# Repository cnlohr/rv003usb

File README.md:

# Using USB on the CH32V003

Ever wanted a 10 cent USB low-speed capable processor? Well, look no further. RV003USB allows you to, in firmware, connect a 10 cent RISC-V to a computer with USB. It is fundamentally just a pin-change interrupt routine that runs in assembly, and some C code to handle higher level functionality.

### It's small!

The bootloader version of the tool can create a HID device, enumerate and allow execution of code on-device in 1,920 bytes of code. Basic HID setups are approximately 2kB, like the Joystick demo.

### It's simple!

The core assembly code is very basic, having both an [interrupt](https://github.com/cnlohr/rv003usb/blob/master/rv003usb/rv003usb.S#L43) and [code to send](https://github.com/cnlohr/rv003usb/blob/master/rv003usb/rv003usb.S#L547). Additionally only around [250 lines of C](https://github.com/cnlohr/rv003usb/blob/master/rv003usb/rv003usb.c) code to facilitate the rest of the USB protocol.

### It's adaptable!

The [core assembly](https://github.com/cnlohr/rv003usb/blob/master/rv003usb/rv003usb.S) code is standardized, and there is also [a c file](https://github.com/cnlohr/rv003usb/blob/master/rv003usb/rv003usb.c) code, to handle different functionality with hid feature requests, control setup events, interrupt endpoints (send and receive) are all done in.

It shows both how to be a normal USB device, as well as how to write programs to run on your PC that can talk to your USB device.

### It requires very little hardware!

 * `U1` is a CH32V003
 * `J1` is a USB type C connector.
 * `R1` 1.5k 5% is required under all configurations, though it may connect D- to DPU or VCC if the intent is for the part to always be on-bus.
 * `U2`, `C1`, `C2` are used to run the CH32V003 at 3.3V.  For USB it should not be run beyond 3.6V.
 * `R2`, `R3` 5.1k resistors are only needed if using a type C connector and you want the host to provide 5V power.

It even supports the SOIC-8 - see this thread: https://github.com/cnlohr/rv003usb/issues/25#issuecomment-1779130408

Optionally 33 or 47 ohm resistors may be placed in-series with D+ and D- to the port to reduce noise and help protect the chip.

### It's configurable

The Pins (Port and GPIO number) used for USB are configured in `usb_config.h`.

~~~C
#define USB_PORT D     // [A,C,D] GPIO Port to use with D+, D- and DPU
#define USB_PIN_DP 3   // [0-4] GPIO Number for USB D+ Pin
#define USB_PIN_DM 4   // [0-4] GPIO Number for USB D- Pin
#define USB_PIN_DPU 5  // [0-7] GPIO for feeding the 1.5k Pull-Up on USB D- Pin; Comment out if not used / tied to 3V3!
~~~

All configured pins need to be on the same GPIO port.

> [!CAUTION]
> Only GPIOs 0-4 can be used for USB D+/D- due to limits of the [c.andi](https://msyksphinz-self.github.io/riscv-isadoc/html/rvc.html#c-andi) instruction which can only hold a 5 bit value. 
> You **cannot use** PC5-PC7 and PD5-PD7 for D+/D-!

A 1,5k pull-up on D- is used to signal the presence of a USB low-speed device on the bus. `USB_PIN_DPU` is designed to control this pull-up, but this is optional. You have three options here:

1. Use `USB_PIN_DPU` to let RV003USB controll the GPIO. You're limited to using the same port as for D+/D-.
2. Comment out `USB_PIN_DPU` and tie the pull-up to 3V3. This frees a GPIO completely and signals device presence constantly. 
3. Comment out `USB_PIN_DPU` and tie it to a GPIO of your choice - even on a different port. You have to signal device presence in your own user-code though.

Even with the pull-up tied to 3V3 you can trigger a USB re-enumeration by pulsing D- low in user-code. Add the otherwise optional 33/47 ohm inline resistors on D+/D- if you plan on doing this!

See [bootloader](bootloader) for additional considerations on the pin configuration if you plan to use the USB bootloader!

> [!NOTE]
> Use `make clean` before `make` whenever you change the configuration in `usb_config.h`

### It's got demos!

Here are the following demos and their statuses...

| Example      | Description | ❖ | 🐧 |
| ------------ | ----------- | --------------- | ------------- |
| [demo_gamepad](https://github.com/cnlohr/rv003usb/tree/master/demo_gamepad) | Extremely simple example, 2-axis gamepad + 8 buttons | `✅` | `✅` |
| [demo_composite_hid](https://github.com/cnlohr/rv003usb/tree/master/demo_composite_hid) | Mouse and Keyboard in one device | `✅` | `✅` |
| [demo_hidapi](https://github.com/cnlohr/rv003usb/tree/master/demo_hidapi) | Write code to directly talk to your project with fully-formed messages. (Works on [Android](https://github.com/cnlohr/androidusbtest)) (Includes WebUSB Demo) | `✅` | `✅` |
| [bootloader](https://github.com/cnlohr/rv003usb/tree/master/bootloader) | CH32V003 Self-bootloader, able to flash itself with minichlink | `✅` | `✅` |

And the following largely incomplete, but proof-of-concept projects:

| Example      | Description | ❖ | 🐧 |
| ------------ | ----------- | --------------- | ------------- |
| [cdc_exp](https://github.com/cnlohr/rv003usb/tree/master/testing/cdc_exp) | Enumerate as a USB Serial port and send and receive Data (incomplete, very simple) | `⚠️` | `✅` | :question: |
| [usb_cdc_uart](https://github.com/cnlohr/rv003usb/tree/master/testing/usb_cdc_uart) | Enumerate as a USB to UART bridge (115200 baud) (very similar issues to cdc_exp, only slightly more complete, tested on linux) | `⚠️` | `✅` | :question: |
| [demo_midi](https://github.com/cnlohr/rv003usb/tree/master/testing/demo_midi) | MIDI-IN and MIDI-OUT | `✅` | `✅` |
| [test_ethernet](https://github.com/cnlohr/rv003usb/tree/master/testing/test_ethernet) | RNDIS Device (note: VERY SLOW) | `⚠️` | `✅` |

Note: CDC In windows likely CAN work, but I can't figure out how to do it.  Linux explicitly blacklists all low-speed USB Ethernet that I could find.  The MIDI example only demonstrates MIDI-OUT.

### It's built on ch32v003fun

[ch32v003fun](https://github.com/cnlohr/ch32v003fun) is a minimal development SDK of sorts for the CH32V003, allowing for maximum flexability without needing lots of code surrounding a HAL.

## General developer notes

### Care surrounding interrupts and critical sections.

You are allowed to use interrupts and have critical sections, however, you should keep critical sections to approximately 40 or fewer cycles if possible.  Additionally if you are going to be using interrupts that will take longer than about 40 cycles to execute, you must enable preemption on that interrup.  For an example of how that works you can check the ws2812b SPI DMA driver in ch32v003fun.  The external pin-chane-interrupt **must** be the highest priority. And it **must never** be preempted.  While it's OK to have a short delay before it is fired, interrupting the USB reception code mid-transfer is prohibited.

### Modifying headers / `usb_config.h`

Note that if you change the pin assignments for your custom hardware in `usb_config.h`, you will need to run `make clean` afterwards (and then run `make`).

## It's still in beta.

This project is not ready for prime time, though it is sort of in a beta phase.  Proof of concept works, lots of demos work.  Maybe you can help out!

`✅` Able to go on-bus and receive USB frames  
`✅` Compute CRC in-line while receiving data  
`✅` Bit Stuffing (Works, tested)  
`✅` Sending USB Frames  
`✅` High Level USB Stack in C  
`✅` Make USB timing more precise.  
`✅` Use SE0 1ms ticks to tune HSItrim  
`✅` Rework sending code to send tokens/data separately.  
`✅` Fix CRC Code  
`✅` Make minichlink able to use bootloader.  
`✅` Optimize high-level stack.  
`✅` Fit in bootloader (NOTE: Need to tighten more)  
`✅` Do basic retiming, at least in preamble to improve timing.  
`✅` Use HID custom messages.  
`✅` Improve sync sled.  I.e. coarse and fine sledding.  
`✅` Abort on non-8-bit-aligned-frames.  
`✅` Make more demos  
`✅` API For self-flashing + `🔳` printf from bootloader  
`🔳` Improve timing on send, for CRC bits.  Currently we are off by about 6 cycles total.  
`❕` Further optimize Send/Receive PHY code. (Please help) 
`❕` Consider a timer-only approach (may never happen)
`⚠️` Enable improved retiming (Requires a few more cycles) (Please help!)  
`⚠️`  Arduino support (someone else will have to take this on)

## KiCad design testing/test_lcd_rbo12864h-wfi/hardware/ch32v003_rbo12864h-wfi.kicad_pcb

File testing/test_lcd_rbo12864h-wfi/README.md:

# rbo12864h-wfi video driver for Linux

You can flash this firmware on a ch32v003 and hook it up to an RBO12864H-WFI.

The display is available from https://www.ronboe.com/ they are very inexpensive but you have to ask for them.

1. Optionally you can flash the bootloader so you can continue to work on this program later.
2. Flash this code to the ch32v003.
3. cd host
4. sudo ./host

The controls allow you to change the contrast, resistor ratio, backlight brightness and cutoff for black/white.

Schematics are located in the hardware/ folder.

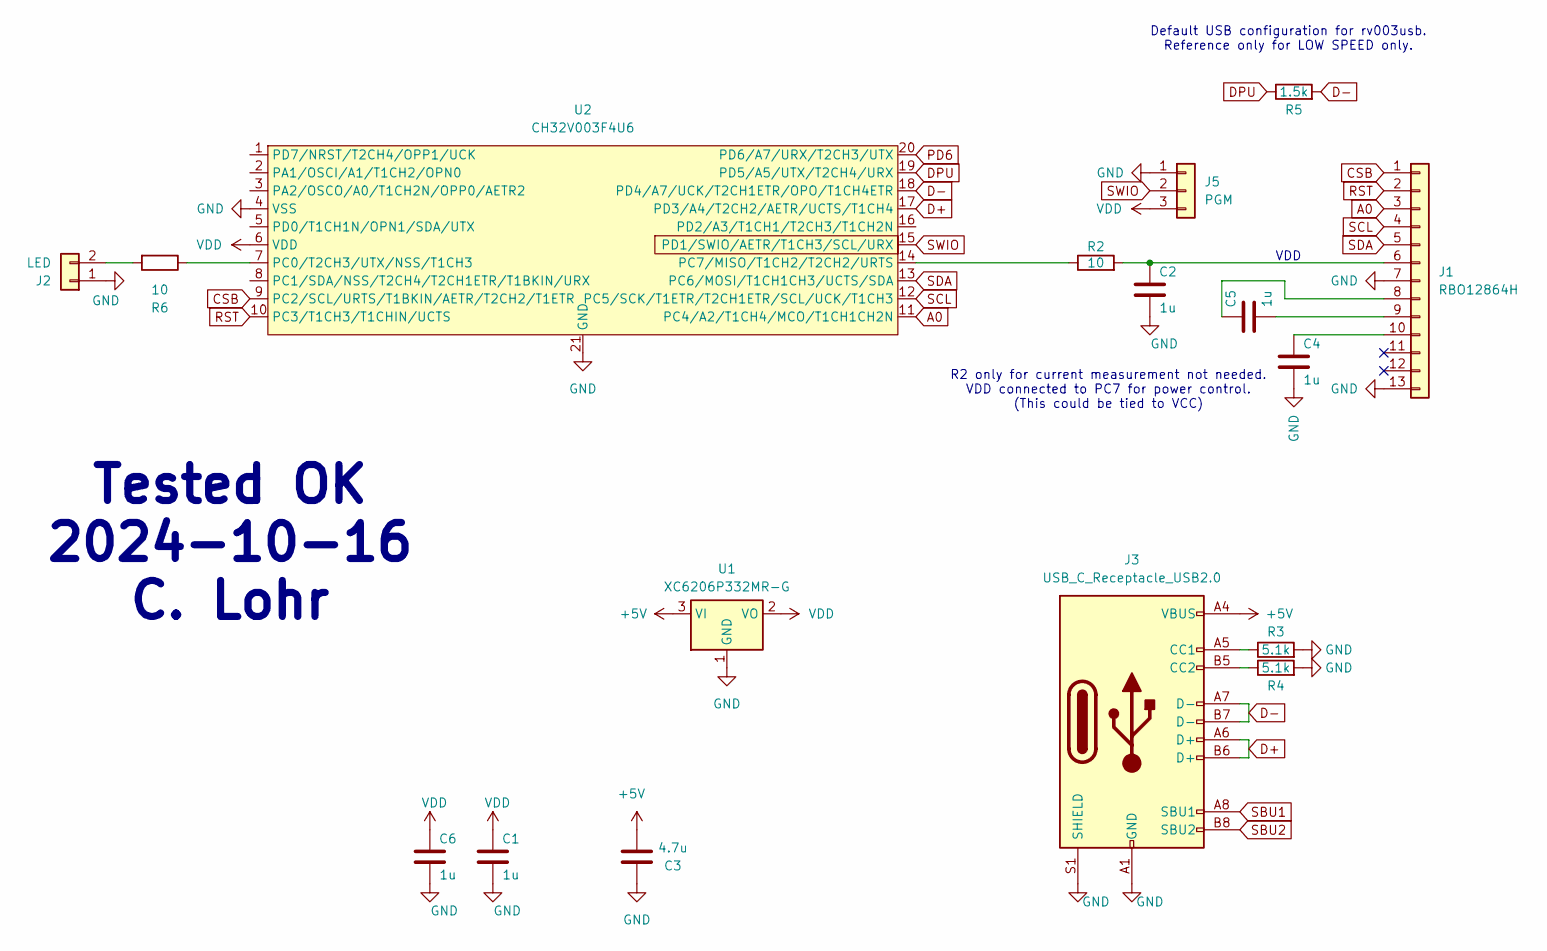
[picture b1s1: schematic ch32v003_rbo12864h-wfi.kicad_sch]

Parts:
C1, C2, C4, C5, C6: 1u; R_0402_1005Metric; LCSC C52923
C3: 4.7u; R_0402_1005Metric; LCSC C23733
J1: RBO12864H; RBO12864H-WFI
J2: LED; PinHeader_1x02_P2.00mm_Vertical
J3: USB_C_Receptacle_USB2.0; USB_C_Receptacle_HRO_TYPE-C-31-M-12; LCSC C2765186
J5: PGM; PinHeader_1x03_P2.54mm_Vertical
R2, R6: 10; R_0402_1005Metric; LCSC C25077
R3, R4: 5.1k; R_0402_1005Metric; LCSC C25905
R5: 1.5k; R_0402_1005Metric; LCSC C25867
U1: XC6206P332MR-G; SOT-23; LCSC C5446
U2: CH32V003F4U6; QFN-20-1EP_3x3mm_P0.4mm_EP1.65x1.65mm; LCSC C5299908

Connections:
+5V: C3.2, J3.A4 (VBUS), J3.A9 (VBUS), J3.B4 (VBUS), J3.B9 (VBUS), U1.3 (VI)
A0: J1.3, U2.11 (PC4/A2/T1CH4/MCO/T1CH1CH2N)
CSB: J1.1, U2.9 (PC2/SCL/URTS/T1BKIN/AETR/T2CH2/T1ETR)
D+: J3.A6 (D+), J3.B6 (D+), U2.17 (PD3/A4/T2CH2/AETR/UCTS/T1CH4)
D-: J3.A7 (D-), J3.B7 (D-), R5.2, U2.18 (PD4/A7/UCK/T2CH1ETR/OPO/T1CH4ETR)
DPU: R5.1, U2.19 (PD5/A5/UTX/T2CH4/URX)
GND: C1.1, C2.1, C3.1, C4.1, C6.1, J1.7, J1.13, J2.1, J3.A1 (GND), J3.A12 (GND), J3.B1 (GND), J3.B12 (GND), J3.S1 (SHIELD), J5.1, R3.2, R4.2, U1.1 (GND), U2.4 (VSS), U2.21 (GND)
unnamed: C2.2, J1.6, R2.2
unnamed: C5.2, J1.8
unnamed: C5.1, J1.9
unnamed: C4.2, J1.10
unnamed: J2.2, R6.2
unnamed: J3.A5 (CC1), R3.1
unnamed: J3.B5 (CC2), R4.1
unnamed: R6.1, U2.7 (PC0/T2CH3/UTX/NSS/T1CH3)
unnamed: R2.1, U2.14 (PC7/MISO/T1CH2/T2CH2/URTS)
PD6: U2.20 (PD6/A7/URX/T2CH3/UTX)
RST: J1.2, U2.10 (PC3/T1CH3/T1CHIN/UCTS)
SBU1: J3.A8 (SBU1)
SBU2: J3.B8 (SBU2)
SCL: J1.4, U2.12 (PC5/SCK/T1ETR/T2CH1ETR/SCL/UCK/T1CH3)
SDA: J1.5, U2.13 (PC6/MOSI/T1CH1CH3/UCTS/SDA)
SWIO: J5.2, U2.15 (PD1/SWIO/AETR/T1CH3/SCL/URX)
VDD: C1.2, C6.2, J5.3, U1.2 (VO), U2.6 (VDD)

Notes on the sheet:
Tested OK 2024-10-16 C. Lohr
Default USB configuration for rv003usb. Reference only for LOW SPEED only.
VDD
R2 only for current measurement not needed. VDD connected to PC7 for power control. (This could be tied to VCC)

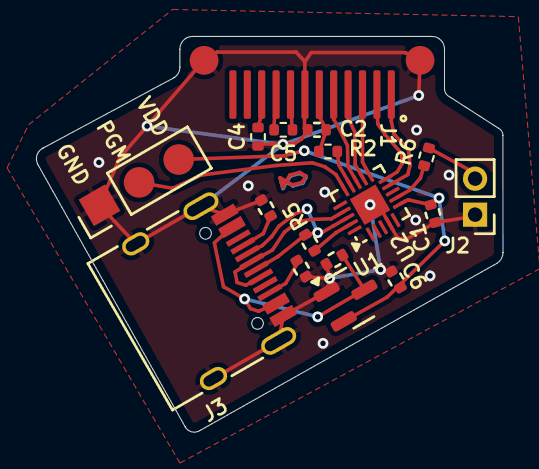
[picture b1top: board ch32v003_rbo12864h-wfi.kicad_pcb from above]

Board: 2 copper layers, 25.9 x 22.0 mm, 17 parts (0 on the bottom side), 21 nets.

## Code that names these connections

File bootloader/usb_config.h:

#ifndef _USB_CONFIG_H
#define _USB_CONFIG_H

//Defines the number of endpoints for this device. (Always add one for EP0). For two EPs, this should be 3.  For one, 2.
#define ENDPOINTS 2

/*	
	CH32V003FUN DevBoard:
	PD3 D+
	PD4 D-
	PD5 D-_PU

	CH32V003J4M6:
	PC1 D+
	PC2 D-
	PC4 D-_PU
*/

#define USB_PORT D     // [A,C,D] GPIO Port to use with D+, D- and DPU
#define USB_PIN_DP 3   // [0-4] GPIO Number for USB D+ Pin
#define USB_PIN_DM 4   // [0-4] GPIO Number for USB D- Pin
//#define USB_PORT_DPU A  // [A,C,D] Override GPIO Port for DPU
#define USB_PIN_DPU 5  // [0-7] GPIO for feeding the 1.5k Pull-Up on USB D- Pin; Comment out if not used / tied to 3V3!

#define RV003USB_OPTIMIZE_FLASH 1

#ifndef __ASSEMBLER__

#include <tinyusb_hid.h>

#ifdef INSTANCE_DESCRIPTORS
//Taken from http://www.usbmadesimple.co.uk/ums_ms_desc_dev.htm
static const uint8_t device_descriptor[] = {
	18, //Length
	1,  //Type (Device)
	0x00, 0x02, //Spec (bcdUSB)
	0x0, //Device Class
	0x0, //Device Subclass
	0x0, //Device Protocol  (000 = use config descriptor)
	0x08, //Max packet size for EP0 (This has to be 8 because of the USB Low-Speed Standard)
	0x09, 0x12, //ID Vendor   //TODO: register this in http://pid.codes/howto/ or somewhere.
	0x03, 0xb0, //ID Product
	0x00, 0x00, //ID Rev (bcdDevice)
	1, //Manufacturer string
	2, //Product string
	3, //Serial string
	1, //Max number of configurations
};


static const uint8_t special_hid_desc[] = { 
  HID_USAGE_PAGE ( HID_USAGE_PAGE_DESKTOP      )                 ,
  HID_USAGE      ( 0xff  )                 , // Needed?
  HID_COLLECTION ( HID_COLLECTION_APPLICATION )                 ,
    HID_REPORT_SIZE ( 8 ),
    HID_REPORT_COUNT ( 127 ) ,
    HID_REPORT_ID    ( 0xaa                                   )
    HID_USAGE        ( 0xff              ) ,
    HID_FEATURE      ( HID_DATA | HID_ARRAY | HID_ABSOLUTE    ) ,
  HID_COLLECTION_END
};


static const uint8_t config_descriptor[] = {  //Mostly stolen from a USB mouse I found.
	// configuration descriptor, USB spec 9.6.3, page 264-266, Table 9-10
	9, 					// bLength;
	2,					// bDescriptorType;
	0x22, 0x00,			// wTotalLength  	

	//34, 0x00, //for just the one descriptor
	
	0x01,					// bNumInterfaces (Normally 1)  (If we need an additional HID interface add here)
	0x01,					// bConfigurationValue
	0x00,					// iConfiguration
	0x80,					// bmAttributes (was 0xa0)
	0x64,					// bMaxPower (200mA)


	//HID THING
	9,					// bLength
	4,					// bDescriptorType
	0,			// bInterfaceNumber (unused, would normally be used for HID)
	0,					// bAlternateSetting
	1,					// bNumEndpoints
	0x03,					// bInterfaceClass (0x03 = HID)
	0x00,					// bInterfaceSubClass
	0xff,					// bInterfaceProtocol
	0,					// iInterface

	9,					// bLength
	0x21,					// bDescriptorType (HID)
	0x10,0x01,		//bcd 1.1
	0x00, //country code
	0x01, //Num descriptors
	0x22, //DescriptorType[0] (HID)
	sizeof(special_hid_desc), 0x00, //Descriptor length XXX This looks wrong!!!

	7, //endpoint descriptor (For endpoint 1)
	0x05, //Endpoint Descriptor (Must be 5)
	0x81, //Endpoint Address
	0x03, //Attributes
	0x08,	0x00, //Size
	0xff, //Interval
};


//Ever wonder how you have more than 6 keys down at the same time on a USB keyboard?  It's easy. Enumerate two keyboards!

#define STR_MANUFACTURER u"cnlohr"
#define STR_PRODUCT      u"rv003usb"
#ifndef STR_SERIAL
#define STR_SERIAL       u"NBTT" // Need to change to BOOT when we finally decide on a flashing mechanism.
#endif

struct usb_string_descriptor_struct {
	uint8_t bLength;
	uint8_t bDescriptorType;
	const uint16_t wString[];
};

const static struct usb_string_descriptor_struct string0 __attribute__((section(".rodata"))) = {
	4,
	3,
	{0x0409}
};
const static struct usb_string_descriptor_struct string1 __attribute__((section(".rodata")))  = {
	sizeof(STR_MANUFACTURER),
	3,
	STR_MANUFACTURER
};
const static struct usb_string_descriptor_struct string2 __attribute__((section(".rodata")))  = {
	sizeof(STR_PRODUCT),
	3,
	STR_PRODUCT
};
const static struct usb_string_descriptor_struct string3 __attribute__((section(".rodata")))  = {
	sizeof(STR_SERIAL),
	3,
	STR_SERIAL
};


// This table defines which descriptor data is sent for each specific
// request from the host (in wValue and wIndex).
const static struct descriptor_list_struct {
	uint32_t	lIndexValue;
	const uint8_t	*addr;
	uint8_t		length;
} descriptor_list[] __attribute__((section(".rodata"))) = {
	{0x00000100, device_descriptor, sizeof(device_descriptor)},
	{0x00000200, config_descriptor, sizeof(config_descriptor)},
	{0x00002200, special_hid_desc, sizeof(special_hid_desc)},
	{0x00000300, (const uint8_t *)&string0, 4},
	{0x04090301, (const uint8_t *)&string1, sizeof(STR_MANUFACTURER)},
	{0x04090302, (const uint8_t *)&string2, sizeof(STR_PRODUCT)},	
	{0x04090303, (const uint8_t *)&string3, sizeof(STR_SERIAL)}
};
#define DESCRIPTOR_LIST_ENTRIES ((sizeof(descriptor_list))/(sizeof(struct descriptor_list_struct)) )

#endif // INSTANCE_DESCRIPTORS

#endif // __ASSEMBLER__
#endif 

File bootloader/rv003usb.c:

// Could be defined here, or in the processor defines.
#define SYSTEM_CORE_CLOCK 48000000
#define SYSTICK_USE_HCLK

#include "ch32v003fun.h"
#include <stdio.h>
#include <string.h>

#define INSTANCE_DESCRIPTORS
#include "rv003usb.h"

// To use time debugging, enable thsi here, and DEBUG_TIMING in the .S
// You must update in tandem
//#define DEBUG_TIMING

// If you don't want to automatically boot into the application, set
// this flag:
#define DISABLE_BOOTLOAD

#define SCRATCHPAD_SIZE 296
extern volatile int32_t runwordpad;
extern uint8_t scratchpad[SCRATCHPAD_SIZE];
uint32_t always0;

struct rv003usb_internal rv003usb_internal_data;

// This is the data actually required for USB.
uint8_t data_receptive;

void SystemInit48HSIUNSAFE( void );

int main()
{
	// Enable GPIOs, TIMERs
	RCC->APB2PCENR = RCC_APB2Periph_GPIOD | RCC_APB2Periph_GPIOC | RCC_APB2Periph_TIM1 | RCC_APB2Periph_GPIOA  | RCC_APB2Periph_AFIO | RCC_APB2Periph_TIM1;

#ifdef DEBUG_TIMING
	// GPIO C0 Push-Pull
	GPIOC->CFGLR = (GPIO_Speed_50MHz | GPIO_CNF_OUT_PP)<<(4*0) |
	               (GPIO_Speed_50MHz | GPIO_CNF_OUT_PP_AF)<<(4*3) | // PC3 = T1C3
	               (GPIO_Speed_50MHz | GPIO_CNF_OUT_PP_AF)<<(4*4) | // PC4 = T1C4
	               (GPIO_Speed_50MHz | GPIO_CNF_OUT_PP)<<(4*2);
#endif

#ifdef DEBUG_TIMING
	{
		// PC4 is MCO (for watching timing)
		GPIOC->CFGLR &= ~(GPIO_CFGLR_MODE4 | GPIO_CFGLR_CNF4);
		GPIOC->CFGLR |= GPIO_CFGLR_CNF4_1 | GPIO_CFGLR_MODE4_0 | GPIO_CFGLR_MODE4_1;
		RCC->CFGR0 = (RCC->CFGR0 & ~RCC_CFGR0_MCO) | RCC_CFGR0_MCO_SYSCLK;

		// PWM is used for debug timing. 
		TIM1->PSC = 0x0000;

		// Auto Reload - sets period
		TIM1->ATRLR = 0xffff;

		// Reload immediately
		TIM1->SWEVGR |= TIM_UG;

		// Enable CH4 output, positive pol
		TIM1->CCER |= TIM_CC3E | TIM_CC3NP;

		// CH2 Mode is output, PWM1 (CC1S = 00, OC1M = 110)
		TIM1->CHCTLR2 |= TIM_OC3M_2 | TIM_OC3M_1;

		// Set the Capture Compare Register value to 50% initially
		TIM1->CH3CVR = 2;
		
		// Enable TIM1 outputs
		TIM1->BDTR |= TIM_MOE;
		
		// Enable TIM1
		TIM1->CTLR1 |= TIM_CEN;
	}
#endif

	// GPIO D3 for input pin change.
	GPIOD->CFGLR =
		(GPIO_CNF_IN_PUPD)<<(4*1) |  // Keep SWIO enabled.
//		(GPIO_Speed_50MHz | GPIO_CNF_OUT_PP)<<(4*DEBUG_PIN) |
		(GPIO_CFGLR_IN_FLOAT)<<(4*USB_DM) |  //PD3 = GPIOD IN
		(GPIO_CFGLR_IN_FLOAT)<<(4*USB_DP) |  //PD4 = GPIOD IN
		(GPIO_CFGLR_OUT_50Mhz_PP)<<(4*USB_DPU);

	// Configure the IO as an interrupt.
	AFIO->EXTICR = 3<<(USB_DP*2); //PORTD.3 (3 out front says PORTD, 3 in back says 3)
	EXTI->INTENR = 1<<USB_DP; // Enable EXT3
	EXTI->FTENR = 1<<USB_DP;  // Rising edge trigger

	// This drive GPIO5 high, which will tell the host that we are going on-bus.
	GPIOD->BSHR = 1<<USB_DPU;

	// enable interrupt
	NVIC_EnableIRQ( EXTI7_0_IRQn );

	// Wait ~5 seconds.
	int32_t localpad = -0xf00000; // Careful: Constant works out to a single lbu instruction.
	while(1)
	{
		if( localpad < 0 )
		{
			if( ++localpad == 0 )
			{
				// Boot to user program.
#ifndef DISABLE_BOOTLOAD
				FLASH->BOOT_MODEKEYR = FLASH_KEY1;
				FLASH->BOOT_MODEKEYR = FLASH_KEY2;
				FLASH->STATR = 0; // 1<<14 is zero, so, boot user code.
				FLASH->CTLR = CR_LOCK_Set;
				PFIC->SCTLR = 1<<31;
#endif
			}
		}
		if( localpad > 0 )
		{
			if( --localpad == 0 )
			{
				/* Scratchpad strucure:
					4-bytes:		LONG( 0x000000aa )
						... code (this is executed) (120 bytes)
					4-bytes:        LONG( 0x1234abcd )

					After the scratchpad is the runpad, its structure is:
					4-bytes:   int32_t  if negative, how long to go before bootloading.  If 0, do nothing.  If positive, execute.
						... 1kB of totally free space.
				*/
				typedef void (*setype)( uint32_t *, volatile int32_t * );
				setype scratchexec = (setype)(scratchpad+4);
				scratchexec( (uint32_t*)&scratchpad[0], &runwordpad );
			}
		}

		uint32_t commandpad = runwordpad;
		if( commandpad )
		{
			localpad = commandpad-1;
			runwordpad = 0;
		}
	}
}

#define ENDPOINT0_SIZE 8 //Fixed for USB 1.1, Low Speed.

void usb_pid_handle_in( uint32_t addr, uint8_t * data, uint32_t endp, uint32_t unused, struct rv003usb_internal * ist )
{
	ist->current_endpoint = endp;
	struct usb_endpoint * e = &ist->eps[endp];

	int tosend = 0;
	uint8_t * sendnow = data-1;
	uint8_t sendtok = e->toggle_in?0b01001011:0b11000011;
	
	// Handle IN (sending data back to PC)
	// Do this down here.
	// We do this because we are required to have an in-endpoint.  We don't
	// have to do anything with it, though.
	if( endp )
	{
		goto send_nada;
	}

	uint8_t * tsend = 0;

	if( e->is_descriptor )
	{
		const struct descriptor_list_struct * dl = &descriptor_list[e->opaque];
		tsend = ((uint8_t*)dl->addr);
	}
	else if( e->opaque == 1 )
	{
		tsend = scratchpad;
	}

	int offset = (e->count_in)<<3;
	tosend = ist->control_max_len - offset;
	if( tosend > ENDPOINT0_SIZE ) tosend = ENDPOINT0_SIZE;
	if( tosend < 0 ) tosend = 0;
	sendnow = tsend + offset;

	if( !tosend || !tsend )
	{
		goto send_nada;
	}
	else
	{
		usb_send_data( sendnow, tosend, 0, sendtok );
	}
	return;
send_nada:

	//always0 -> //CRC = 0
	usb_send_data( (uint8_t*)&always0, 2, 2, sendtok );  //DATA = 0, 0 CRC.
}

void usb_pid_handle_data( uint32_t this_token, uint8_t * data, uint32_t which_data, uint32_t length, struct rv003usb_internal * ist )
{
	//Received data from host.
	int cep = ist->current_endpoint;
	struct usb_endpoint * e = &ist->eps[cep];

	// Alrady received this packet.
	if( e->toggle_out != which_data )
	{
		goto just_ack;
	}
	// XXX NOTE:  		e->toggle_out = !e->toggle_out; should be here.
	if( cep == 0 )
	{
		e->toggle_out = !e->toggle_out;
		if( ist->setup_request )
		{
			struct usb_urb * s = __builtin_assume_aligned( (struct usb_urb *)(data+1), 4 );

			uint32_t wvi = s->lValueLSBIndexMSB;
			//Send just a data packet.
			e->count_in = 0;
			e->count_out = 0;
			e->is_descriptor = 0;
			ist->setup_request = 0;
			ist->control_max_len = 0;

			if( s->wRequestTypeLSBRequestMSB == 0x01a1 )
			{
				// Class read request.
				uint32_t wlen = s->wLength;
				if( wlen > sizeof(scratchpad) ) wlen = SCRATCHPAD_SIZE;
				// The host wants to read back from us.
				ist->control_max_len = wlen;
				e->opaque = 1;
			}
			else if( s->wRequestTypeLSBRequestMSB == 0x0921 )
			{
				// Class write request.
				ist->control_max_len = SCRATCHPAD_SIZE;
				runwordpad = 1; //request stoppage.
				e->opaque = 2;
			}
			else if( (s->wRequestTypeLSBRequestMSB & 0xff80) == 0x0680 )
			{
				int i;
				const struct descriptor_list_struct * dl;
				for( i = 0; i < DESCRIPTOR_LIST_ENTRIES; i++ )
				{
					dl = &descriptor_list[i];
					if( dl->lIndexValue == wvi )
					{
						// Send back descriptor.
						e->opaque = i;
						e->is_descriptor = 1;
						uint16_t swLen = s->wLength;
						uint16_t elLen = dl->length;
						ist->control_max_len = (swLen < elLen)?swLen:elLen;
						break;
					}
				}

				goto just_ack;
			}
			else if( s->wRequestTypeLSBRequestMSB == 0x0500 )
			{
				//Set address.
				ist->my_address = wvi;
				e->opaque = 0;
			}
			else
			{
				e->opaque = 0;
			}
		}
		else
		{
			// Continuing data.
			if( e->opaque == 2 )
			{
				uint8_t * start = &scratchpad[e->count_out];
				int l = length-3;
				int i;
				for( i = 0; i < l; i++ )
					start[i] = data[i+1];//((intptr_t)data)>>(i*8);
				e->count_out += l;

				if( e->count_out >= SCRATCHPAD_SIZE )
				{
					// If the last 4 bytes are 0x1234abcd, then we can go!
					uint32_t * last4 = (uint32_t*)(start + 4);					
					if( *last4 == 0x1234abcd )
					{
						*last4 = 0;
						runwordpad = 0x200; // Request exectution
					}
					e->opaque = 0;
				}
			}
			// Allow user code to receive data.
		}
	}
just_ack:
	{
		//Got the right data.  Acknowledge.
		usb_send_data( 0, 0, 2, 0xD2 ); // Send ACK
	}
	return;
}

#ifndef REALLY_TINY_COMP_FLASH

void usb_pid_handle_ack( uint32_t dummy, uint8_t * data, uint32_t dummy1, uint32_t dummy2, struct rv003usb_internal * ist  )
{
	struct usb_endpoint * e = &ist->eps[ist->current_endpoint];
	e->toggle_in = !e->toggle_in;
	e->count_in++;
	return;
}

//Received a setup for a specific endpoint.
void usb_pid_handle_setup( uint32_t addr, uint8_t * data, uint32_t endp, uint32_t unused, struct rv003usb_internal * ist )
{
	ist->current_endpoint = endp;
	struct usb_endpoint * e = &ist->eps[endp];

	e->toggle_out = 0;
	e->count_in = 0;
	e->toggle_in = 1;
	ist->setup_request = 1;
}

#endif

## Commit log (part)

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2023-05-19 Mid-stream update.
2023-05-19 mid-stream update
2023-05-19 End of stream 3.
2023-05-19 Getting very close. 32 cycles for main, 34 for write.
2023-05-19 Basic model in place. Ready for stream #4
2023-05-21 Update mid-stream
2023-05-21 Update CRCs so that they are 0 if correct, and we are getting good CRCs on both DATA and SETUP frames!
2023-05-21 Mid-stream push
2023-05-21 Mid-stream checkin - code compiles.
2023-05-21 End of stream - we're driving the line, it's just clamping.
2023-05-27 IT'S ALLIIVVEE
2023-05-27 End of stream 5. It works!
2023-05-27 Add bins
2023-05-28 Remove unneeded files.
    Remove printf to understand space constraints.
2023-05-28 Update branch
2023-05-28 Remove bin/elf
2023-05-28 a few more tweaks
2023-05-29 At 2588 / 2712
2023-05-29 2484/2408 now. Time to branch.
2023-05-29 2068/2140
2023-05-29 2060/2124
2023-05-29 1912/1924
2023-05-29 1896/1908
2023-05-29 1920/1908 - working bootloader
2023-05-29 Add more notes for USB examples.
2023-05-29 Fix name of boot loader.
2023-05-29 1836/1856
2023-05-29 1808/1824
2023-05-29 Fix bit stuffing.
2023-05-29 Able to talk at >50kBytes/s.
2023-05-30 Working demo with updated USB stack.
2023-05-30 A little cleaner. Still need workss
2023-05-30 Getting very close to a fully working demo
2023-05-30 Tweaks
2023-05-31 It works, full bore. But, weeeiirrdd timing rules.
2023-05-31 Working over a reasonable range! We might be able to make this happen.
2023-05-31 Refactora bit to get a few bytes back.
2023-06-01 It fits in 1888 bytes
2023-06-01 working flash code over USB
2023-06-01 Bootie boot boooo boooo boott ee llloooaaaddd rrruuunnn rraaammmyyyy
2023-06-01 Move examples
2023-06-01 I think this is what I am going with for now
2023-06-03 Update with gamepad
2023-06-04 Getting closer to a self-adjusting preamble
2023-06-04 Significantly improve USB sync timing.
    Now we have leeway of -4/+6 cycles!
2023-06-04 Update readme to reflect improvement.
2023-06-05 jump-delay some more functions.
2023-06-05 More optimizations, and allow for word-at-a-time accesses for general struct's.
2023-06-05 Almost able to boot to user code.
2023-06-05 Update bootloader code
2023-06-05 Update to newe bootloader
2023-06-18 Improve bootloader, get it closer to what we need.
2023-06-19 Almost functional bootloader
2023-06-21 Working bootloader with minichlink.
2023-07-03 Firs stab start at running from RAM
2023-07-21 fix/clean up bit stuffing, use seqz, remove pin restriction
2023-07-30 Refactor, making it easier to develop.
2023-07-30 Forgot to commit .c file + Minimize needed demo code.
2023-07-30 Refactor count_in and count_out into count.
2023-07-30 Improve bootloader, including names, etc.
2023-07-30 Cleanup gamepad
2023-07-30 Add a composite demo. Mouse and keyboard.
2023-07-30 Fix glitch in markdown
2023-07-30 Update notes and add documentation to app that uses this.
2023-07-30 Add a sandbox and CDC experiments.
2023-07-30 Correct firmware side for running on Windows
2023-07-30 Update Windows side of custom USB device.
2023-07-30 Add timeout for when feature reports aren't working.
2023-07-30 Use user-defined class
2023-07-31 Further cleanup descriptors
2023-08-01 Update ch version + Switch to correct naming for empty sending.
2023-08-01 Refactor a lot of the user hooks, to be #definable.
2023-08-01 Try switching opaque mode.
2023-08-01 Very close to the new refactor
2023-08-02 Getting close to a functional system.
2023-08-02 Bump submodule
2023-08-02 Tweak
2023-08-03 Update with working Android
2023-08-03 Clean / tighten up some of the code
2023-08-03 Looks like midi might be possible.
2023-08-03 remove extra definition
2023-08-03 Move cdc lib + add note to come back and check CDC.
2023-08-04 RNDIS Almost running in Windows
2023-08-05 Saved another few bits by ironing out the weird +1 logic with data.
2023-08-05 ENUMERATION IN WINDOWS
2023-08-06 General update
2023-08-06 Windows thinks this is good.
2023-08-06 Sending and receiving frames.
2023-08-06 Major refactor / feature rename.
2023-08-06 Get closer to a working CDC
2023-08-06 Cleanup debugging for missing string descriptors + CDC Serial Example
2023-08-06 Enumerate list of what works.
2023-08-06 cleanup
2023-08-06 Fix checkmarks
2023-08-06 Bump with real emojis
2023-09-14 Add a touch demo
2023-09-23 fix: bootloader fails to build
2023-10-19 Update without mini dots
2023-10-19 Aad explaination for hookup
2023-10-19 cleanup reasoning about flippage
2023-10-19 ADd note about optional resistors.
2023-10-19 Oops fix grammar
2023-11-02 MIDI in and out
2023-11-03 MIDI out to square wave on PC0 and PC1
2023-11-05 Update touchpad code.
2023-12-15 Change "go nowhere" location for debug timer when disabled
    0x44 is the BDTR register, which incidentally contains the output enable bit (and breaks PWM output). 0x58 at least doesn't contain anything according to the data sheet and doesn't break anything for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
2023-12-18 Update top demo + explain a little about the HIDAPI
2023-12-18 Add feature for using hidapitester and add documentation for it.
2023-12-19 remove option -U as it breaks flashing on windows and is not documented
2023-12-19 add make_win.bat to build and flash on windows
2023-12-19 fix bootloader USB and HID descriptor
2023-12-19 just formatting
2023-12-21 Fix the mouse composite HID report descriptor.
2024-01-02 make bootloader PORT configurable
2024-01-02 GPIO setup without touching other pins (like SWIO)
2024-01-05 refactor optional USB_DPU
    This is uglier but saves 20 bytes of code
2024-01-06 add optional BOOTLOADER_KEEP_PORT_CFG to save some space
2024-01-06 add bootloader timeout configuration with Host detection
2024-01-14 add Bootloader Button feature
2024-01-27 made USB_DPU optional in rv003usb
2024-01-27 fix composite_hid descriptor and add re-enumeration delay
    The composite_hid descriptor didn't work on Windows. Witch this change it works on Windows, Linux and MacOS. Also added a delay to ensure re-enumeration after bootloader or reset.
2024-01-27 reduce re-enumeration delay
    reduced to 1ms. USB Spec actually demands just >2.5µs which makes the delay obsolete because SystemInit() keeps the pin low for ~200µs. However, if the system is reset/initialized in any other way, t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
2024-02-18 Update README.md for pin-change note
2024-02-21 correct usage of USB_DP/USB_DM to avoid confusion
    Before this, USB_DP was used for D- and USB_DM was used for D+ due to historical reasons during development of the USB stack. This however is frustratingly confusing, so this should fix it.
2024-02-22 throw error for older usb_config.h files
    Earlier usb_config.h had USB_DM/USB_DP swapped.
    Alert user to correct them!
2024-02-24 rename DM/DP to end confusion
    Before this, USB_DP was used for D- and USB_DM was used for D+ due to historical reasons during development of the USB stack. This however is frustratingly confusing, so this should fix it.
2024-02-24 fallback and issue warning for users with USB_DM/USB_DP
2024-02-25 add bootloader readme
2024-02-25 update main readme with pin configuration info and other notes
2024-02-25 throw error if FUNCONF_SYSTICK_USE_HCLK is not set
2024-03-15 Revert "throw error if FUNCONF_SYSTICK_USE_HCLK is not set"
    This reverts commit d79484df60a18f5767588498d3e66512530e8478.
2024-03-24 make port configurable for DPU pin
2024-03-24 only set DPU pin when pin is defined
2024-04-23 Forgot missing example
2024-05-04 fix timeout
2024-05-27 Closes #58
2024-06-20 spell check
2024-07-17 Bump submodule (tested,working)
2024-09-01 Fix bootload not timing out if no button defined.
2024-09-01 Bump submodule (tested)
2024-09-28 Update getting closer
2024-09-28 Made some progress
2024-09-29 Getting closer
2024-09-29 Got something interesting cookin' with timers.
2024-09-29 Ok no really going to sleep
2024-10-16 Update with example project being an LCD video adapter.
2024-10-16 Update code to include mechanism to flash option bytes.
2024-10-16 Add readme
2024-10-16 Bump to master + add stats for host.
2024-10-20 Add software reboot functionality
2024-10-25 Cleaner version
2024-11-11 Fine tune the timing some more
2024-11-11 Move swio programmer into its own place.
2024-11-11 Significantly improve reliability of flashing.
2024-11-11 Update schematic and diagram
2024-11-11 Forgot readme
2024-11-11 Update note about being good for SOIC-8
2024-11-29 Add reboot-into-bootloader-by-hidapi
2024-12-08 Make default behavior for bootloader to enable BOOST.
2025-02-09 Add option bytes build note
2025-02-09 Upgrade to new version of ch32v003fun
2025-02-09 Upgrade rvswio project
2025-02-09 Cleanup a little
2025-02-15 Fix #82
    This has been tested today with a tssop20 ch32v003.
    I've confirmed that it builds and flashes using the esp32s2funprog programmer.
    I've confirmed that the demo_gamepad example works (it enumerates as a low-speed USB device).
2025-02-19 Fix DM unlock procedure
2025-02-19 Fix flags
2025-02-19 Forgot #if
2025-02-19 Fix issue with poll_input
2025-03-01 Fixup for ch32v00x (untested)
2025-03-01 Fixup for 00x
2025-03-06 Forgot to remove one extra file
2025-03-07 Bring the programmer up to date to in-line with the esp32-s2 programmer
2025-03-07 Move the programmer to be a properly released device
2025-03-20 Update ch32v003fun to latest
2025-03-28 Fixed RV003USB_USE_REBOOT_FEATURE_REPORT
2025-04-06 Improve additional EXTI. Add example code for it
2025-04-06 Fix + cleanup
2025-04-13 Make sure bootloader partition doesn't have leftover junk. Fix typo.
2025-04-16 Fix XOR not usable in LD on some systems
2025-04-22 Update swio_self.h to work with latest ch32fun
2025-05-08 add cdc demo
2025-05-08 authoring and docs
2025-05-08 one typo... yup
2025-05-09 edits as requested
2025-05-09 typo
2025-05-13 * Update to new folder locations * Allow setting RVBB_REMAP to 0
2025-05-21 updated the readme as well
2025-05-27 add warning about bootloader entry condition
2025-05-27 rvswio: add power pin control macros
2025-08-04 Update README. Fix bug in microblob functions for ch585
2025-08-07 Fixed bcdUSB field and bcdDevice field values: - bcdUSB 0x0110 (USB 1.1) to 0x0200 (USB 2.0) - bcdDevice 0x0200 to 0x0000
2025-08-19 Fix receiving led keyboard's statuses in demo_composite_hid
2025-08-19 Update log message
2025-08-20 better feature description
2025-08-21 Put the reset flow into one function and make the binary smaller: - Remove the forgotten FLASH->CTLR = CR_LOCK_Set; - Add sysreset_flow function before boot_usercode and replace
2025-08-21 Move images off repo
2025-08-22 Add trackball example (#109)
    * add trackball example
    * cleaner version
    * better text
    * better feature description
    * Move images off repo
    * replace spaces with tabs
2025-08-22 Fixed bcdUSB field and bcdDevice field values: (#105)
    - bcdUSB 0x0110 (USB 1.1) to 0x0200 (USB 2.0)
    - bcdDevice 0x0200 to 0x0000
2025-08-23 Change the way that puts the reset flow into one function to better: - Remove sysreset_flow function - Change to using only boot_usercode function
2025-09-14 Add PlatformIO compatibility
2025-09-14 Add includes for necessary types
2025-09-14 Enable usage as PlatformIO ch32v003fun library
2025-10-01 Change delay from 1 ms to 100 ms before disable SWIO
2025-10-02 Remove the contamination of debug code for my board.
2025-10-25 Testing - Low Speed Xinput (XUSBI)
2025-11-05 Fix xinput platformio environment name
2025-11-05 Testing - Implement vibration out endpoint handling
2025-12-21 Update ch32v003fun submodule
2025-12-25 Use ch32fun instead of ch32v003fun
    I hope I didn't miss anything, `make all` ran through w/o any problems…
2025-12-28 Always load hsitrim, even for a 0 windup
    Saves 4 bytes and I don't think we should handle it as a special case.
    If we get here, we *still* have deviance and could (due to e.g.
    temperature changes) be returning from a non-zero state
2025-12-28 Use SYSTICK as a base register
    Uses only a LUI, not an addi afterwards as well, which can be done with
    an offset load
2025-12-28 Use ENDP_OFFSET as offset instead of adding it
2026-01-04 Experiments with UUID as Serial Number
2026-01-04 Made STR_SERIAL redefinable. Readme
2026-03-15 Fix SysTicK_IRQn naming
2026-03-15 Correct usage of make and fail on build error
2026-03-15 Fix gamepad environment actually building the right source code
2026-04-23 Add support for ch32v00x
2026-05-06 Add v006 bootloader. Update v003 bootloader.
2026-05-29 Fix clearing of RAM in tiny boot
